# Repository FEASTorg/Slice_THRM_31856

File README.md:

<div align="center">
  <!-- Title: -->
  
  <h2><a href="https://github.com/uwo-fast/Slice_THRM"> Slice THRM </a></h2>
  <!-- Labels: -->
  <!-- First row: -->

  <a href="https://certification.oshwa.org/">
    
    <!-- img src="https://img.shields.io/badge/OSHWA-Certified-darkgreen?style=flat-square" height="20" alt="OSHWA" -->       <!-- img src="https://img.shields.io/badge/OSHWA-Pending-darkorange?style=flat-square" height="20" alt="OSHWA" -->
  </a>

  <!-- Second row: -->
  <br>

  <!-- Short description: -->
  <h3>Thermocouple Reader Slice for BREAD.</h3>
</div>

## Introduction
A BREAD slice that reads four thermocouples. Each channel has its own
MAX31856 (cold-junction compensated, linearized, types B/E/J/K/N/R/S/T),
read by the slice's Arduino Nano over one shared SPI bus.

## Project Overview

### Channels

| Channel | Terminal | Converter | Nano CS | Nano DRDY | FAULT (through U2) |
| ------- | -------- | --------- | ------- | --------- | ------------------ |
| 1 | J4 (pin 1 T+, pin 2 T-) | U4 | D6 | A3 | A7 with D10 low |
| 2 | J5 | U5 | D7 | A2 | A7 with D10 high |
| 3 | J6 | U6 | D8 | A1 | A6 with D10 low |
| 4 | J7 | U7 | D9 | A0 | A6 with D10 high |

FAULT and DRDY are active low. The four FAULT lines reach the Nano's
analog-only pins A6/A7 through U2 (CD74HC4053): D10 drives S1 and S2
together, so one D10 level selects channels 1 and 3, the other 2 and 4.
FAULT1-4 have 10k pull-ups to 3.3 V, so an idle line reads about 3.3 V
on the 0-5 V ADC and an asserted fault reads near 0 V.

### SPI

- Shared SCK (D13), SDI/MOSI (D11), SDO/MISO (D12); one CS per channel.
- SPI mode 1 or 3: the MAX31856 needs CPHA = 1 and accepts either
  clock polarity (data sheet 19-7534 Rev 0, Table 5).
- SCK up to 4 MHz (16 MHz / 4). The MAX31856 allows 5 MHz; the level
  buffers add a few ns each way, so check SDO timing on the bench before
  going faster than 4 MHz.
- D10 is the AVR's hardware SS pin; it is an output here (FAULT_SW), which
  keeps the SPI peripheral in master mode.

### 3.3 V domain and level shifting

The MAX31856s run from +3V3 (U3, MIC5225-3.3, 150 mA). The Nano is 5 V.

- U8 (74LVC245A, on +3V3) passes CS1-4, SCK and SDI from the Nano to the
  converters at 3.3 V. Its inputs accept 5 V.
- U9 (74AHCT245, on +5V) passes SDO and DRDY1-4 back to the Nano. Its TTL
  inputs (VIH 2.0 V) read the 3.3 V outputs with margin.
- R21-R24 hold CS1-4 high while the Nano is in reset, so no converter is
  selected. R25 (10k) holds SDO low when no converter drives it.
- U9 drives the Nano's MISO (D12) at all times: program the Nano over USB,
  not through an ICSP header plugged into the Nano.

### Qwiic (J1)

J1 is a 3.3 V Qwiic port. Its supply pin is on +3V3 (U3), and U10
(PCA9306) translates between it and the slice's 5 V I2C bus (A4/A5 and
the bus connector). R33/R34 pull the 5 V side up to +5V and R31/R32 pull
the Qwiic side up to +3V3. U10's EN and VREF2 are tied and held at +5V
through R30 (200k), with C31 (100 pF) on VREF2, so the translator is
always on.

The Qwiic device's current comes from U3 (150 mA), which also feeds the
four MAX31856s and U8.

### Firmware

`firmware/` is empty; firmware is tracked separately.

## Installation
[Provide instructions for installing any necessary software or hardware components.]

## Usage
[Explain how to use the project. Include examples and screenshots if applicable.]

### Basic Usage
[Provide basic usage instructions.]

### Advanced Usage
[Provide advanced usage instructions, including any optional features or configurations.]

## Documentation
[Link to the detailed documentation if available. Provide instructions on how to access and navigate the documentation.]

## Contributing
[Explain how others can contribute to the project. Include guidelines for submitting issues, pull requests, and any coding standards.]

### Code of Conduct
[Link to the project's code of conduct if available.]

## License
[State the license under which the project is distributed. Include a link to the full license text.]

## Acknowledgements
[Acknowledge any contributors, collaborators, funding sources, or organizations that supported the project.]

## Contact
[Provide contact information for the project maintainer(s) or lead researcher(s). Include an email address or a link to a contact form.]

---

<div align="center">
  
</div>

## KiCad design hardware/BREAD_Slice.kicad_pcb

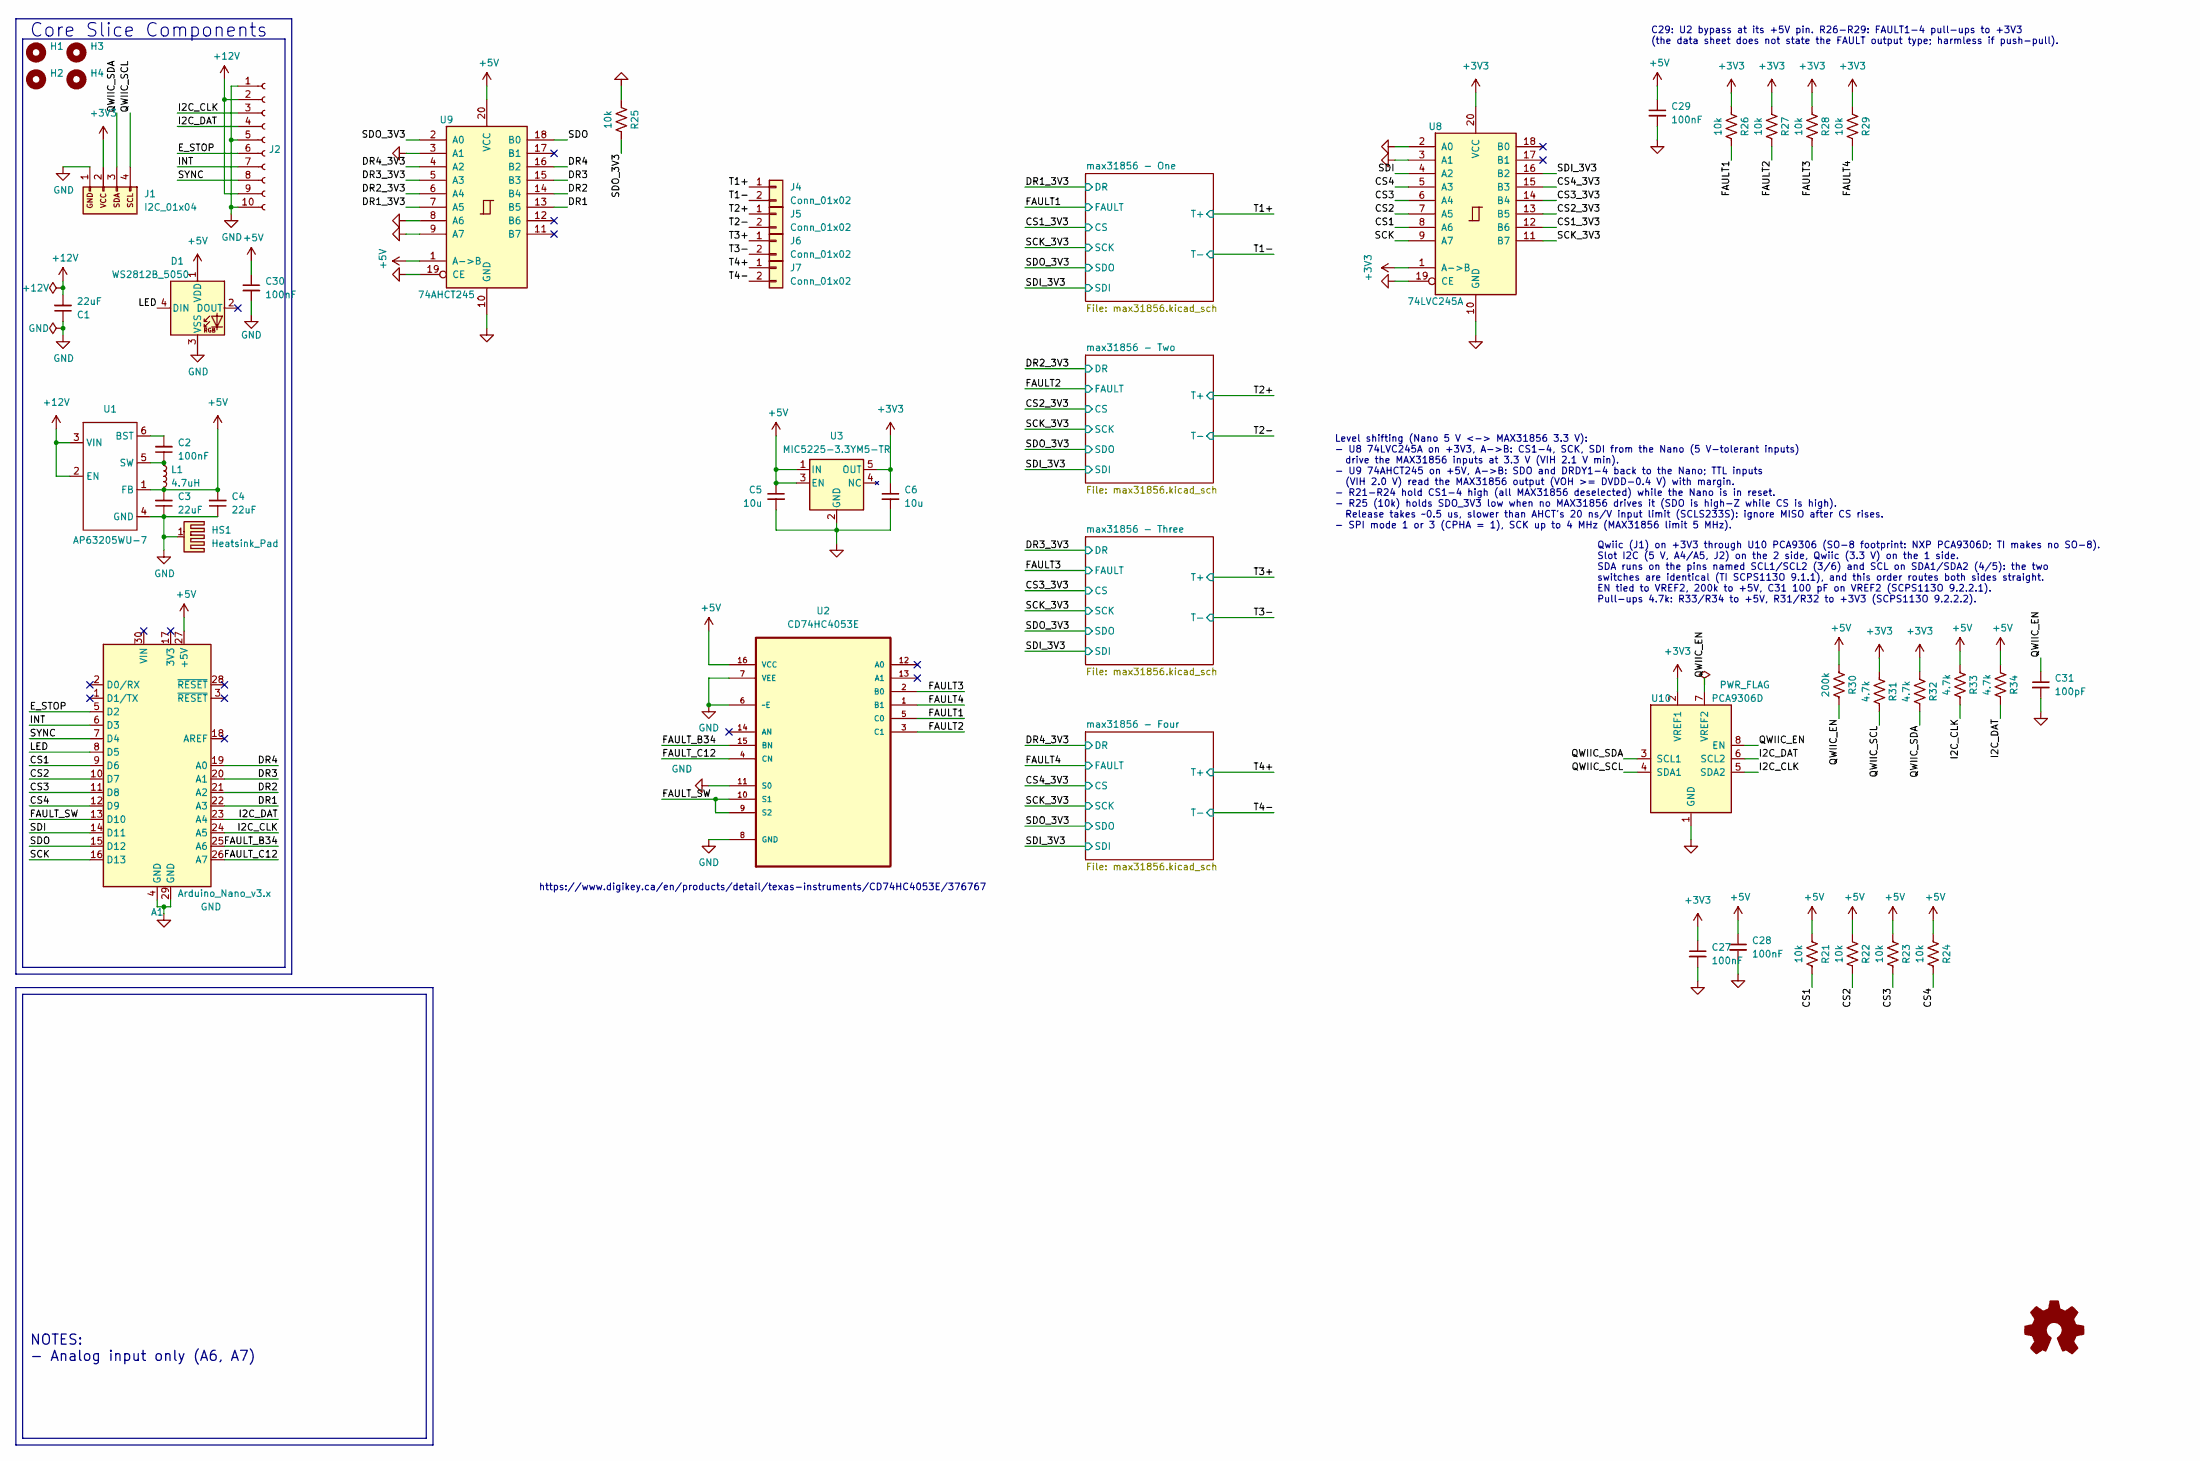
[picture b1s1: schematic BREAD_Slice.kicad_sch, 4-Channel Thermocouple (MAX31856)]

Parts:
A1: Arduino_Nano_v3.x; Arduino_Nano
C1, C3, C4: 22uF; C_1206_3216Metric
C2: 100nF; C_1206_3216Metric
C5, C6: 10u; C_1206_3216Metric
C27, C28, C29, C30: 100nF; C_0805_2012Metric
C31: 100pF; C_0603_1608Metric
D1: WS2812B_5050; WS2812-5050-4PIN
H1, H2, H3, H4: MountingHole; MountingHole_5mm
HS1: Heatsink_Pad; Thermal_Pad
J1: I2C_01x04; JST_SH_SM04B-SRSS-TB_1x04-1MP_P1.00mm_Horizontal
J2: Conn_01x10_Female; PinSocket_1x10_P2.54mm_Horizontal
J4, J5, J6, J7: Conn_01x02; TerminalBlock_4Ucon_1x02_P3.50mm_Horizontal
L1: 4.7uH; L_1210_3225Metric
R21, R22, R23, R24, R25, R26, R27, R28, R29: 10k; R_0805_2012Metric
R30: 200k; R_0805_2012Metric
R31, R32, R33, R34: 4.7k; R_0805_2012Metric
U1: AP63205WU-7; TSOT-23-6
U2: CD74HC4053E; DIP254P762X508-16; MPN CD74HC4053E
U3: MIC5225-3.3YM5-TR; SOT-23-5
U8: 74LVC245A; TSSOP-20_4.4x6.5mm_P0.65mm
U9: 74AHCT245; TSSOP-20_4.4x6.5mm_P0.65mm
U10: PCA9306D; SO-8_3.9x4.9mm_P1.27mm

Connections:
+3V3: C6.1, C27.1, J1.2, R26.1, R27.1, R28.1, R29.1, R31.1, R32.1, U3.5 (OUT), U8.1 (A->B), U8.20 (VCC), U10.2 (VREF1); also elsewhere on the board
+5V: A1.27 (+5V), C3.2, C4.2, C5.1, C28.1, C29.1, C30.1, D1.1 (VDD), L1.2, R21.1, R22.1, R23.1, R24.1, R30.1, R33.1, R34.1, U1.1 (FB), U2.16 (VCC), U3.1 (IN), U3.3 (EN), U9.1 (A->B), U9.20 (VCC)
+12V: C1.2, J2.2, J2.9, U1.2 (EN), U1.3 (VIN)
/CS1: A1.9 (D6), R21.2, U8.8 (A6)
/CS1_3V3: U8.12 (B6); also elsewhere on the board
/CS2: A1.10 (D7), R22.2, U8.7 (A5)
/CS2_3V3: U8.13 (B5); also elsewhere on the board
/CS3: A1.11 (D8), R23.2, U8.6 (A4)
/CS3_3V3: U8.14 (B4); also elsewhere on the board
/CS4: A1.12 (D9), R24.2, U8.5 (A3)
/CS4_3V3: U8.15 (B3); also elsewhere on the board
/DR1: A1.22 (A3), U9.13 (B5)
/DR1_3V3: U9.7 (A5); also elsewhere on the board
/DR2: A1.21 (A2), U9.14 (B4)
/DR2_3V3: U9.6 (A4); also elsewhere on the board
/DR3: A1.20 (A1), U9.15 (B3)
/DR3_3V3: U9.5 (A3); also elsewhere on the board
/DR4: A1.19 (A0), U9.16 (B2)
/DR4_3V3: U9.4 (A2); also elsewhere on the board
/E_STOP: A1.5 (D2), J2.6
/FAULT1: R26.2, U2.5 (C0); also elsewhere on the board
/FAULT2: R27.2, U2.3 (C1); also elsewhere on the board
/FAULT3: R28.2, U2.2 (B0); also elsewhere on the board
/FAULT4: R29.2, U2.1 (B1); also elsewhere on the board
/FAULT_B34: A1.25 (A6), U2.15 (BN)
/FAULT_C12: A1.26 (A7), U2.4 (CN)
/FAULT_SW: A1.13 (D10), U2.9 (S2), U2.10 (S1)
/I2C_CLK: A1.24 (A5), J2.3, R33.2, U10.5 (SDA2)
/I2C_DAT: A1.23 (A4), J2.4, R34.2, U10.6 (SCL2)
/INT: A1.6 (D3), J2.7
/LED: A1.8 (D5), D1.4 (DIN)
/QWIIC_EN: C31.1, R30.2, U10.7 (VREF2), U10.8 (EN)
/QWIIC_SCL: J1.4, R31.2, U10.4 (SDA1)
/QWIIC_SDA: J1.3, R32.2, U10.3 (SCL1)
/SCK: A1.16 (D13), U8.9 (A7)
/SCK_3V3: U8.11 (B7); also elsewhere on the board
/SDI: A1.14 (D11), U8.4 (A2)
/SDI_3V3: U8.16 (B2); also elsewhere on the board
/SDO: A1.15 (D12), U9.18 (B0)
/SDO_3V3: R25.2, U9.2 (A0); also elsewhere on the board
/SYNC: A1.7 (D4), J2.8
/T1+: J4.1; also elsewhere on the board
/T1-: J4.2; also elsewhere on the board
/T2+: J5.1; also elsewhere on the board
/T2-: J5.2; also elsewhere on the board
/T3+: J6.1; also elsewhere on the board
/T3-: J6.2; also elsewhere on the board
/T4+: J7.1; also elsewhere on the board
/T4-: J7.2; also elsewhere on the board
GND: A1.4 (GND), A1.29 (GND), C1.1, C3.1, C4.1, C5.2, C6.2, C27.2, C28.2, C29.2, C30.2, C31.2, D1.3 (VSS), HS1.1, J1.1, J2.1, J2.5, J2.10, R25.1, U1.4 (GND), U2.6 (~E), U2.7 (VEE), U2.8 (GND), U2.11 (S0), U3.2 (GND), U8.2 (A0), U8.3 (A1), U8.10 (GND), U8.19 (CE), U9.3 (A1), U9.8 (A6), U9.9 (A7), U9.10 (GND), U9.19 (CE), U10.1 (GND); also elsewhere on the board
unnamed: C2.2, U1.6 (BST)
unnamed: C2.1, L1.1, U1.5 (SW)

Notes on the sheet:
NOTES: - Analog input only (A6, A7)
Core Slice Components
https://www.digikey.ca/en/products/detail/texas-instruments/CD74HC4053E/376767
Level shifting (Nano 5 V <-> MAX31856 3.3 V): - U8 74LVC245A on +3V3, A->B: CS1-4, SCK, SDI from the Nano (5 V-tolerant inputs) drive the MAX31856 inputs at 3.3 V (VIH 2.1 V min). - U9 74AHCT245 on +5V, A->B: SDO and DRDY1-4 back to the Nano; TTL inputs (VIH 2.0 V) read the MAX31856 output (VOH >= 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
C29: U2 bypass at its +5V pin. R26-R29: FAULT1-4 pull-ups to +3V3 (the data sheet does not state the FAULT output type; harmless if push-pull).
Qwiic (J1) on +3V3 through U10 PCA9306 (SO-8 footprint: NXP PCA9306D; TI makes no SO-8). Slot I2C (5 V, A4/A5, J2) on the 2 side, Qwiic (3.3 V) on the 1 side. SDA runs on the pins named SCL1/SCL2 (3/6) and SCL on SDA1/SDA2 (4/5): the two switches are identical (TI SCPS113O 9.1.1), and this order ro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

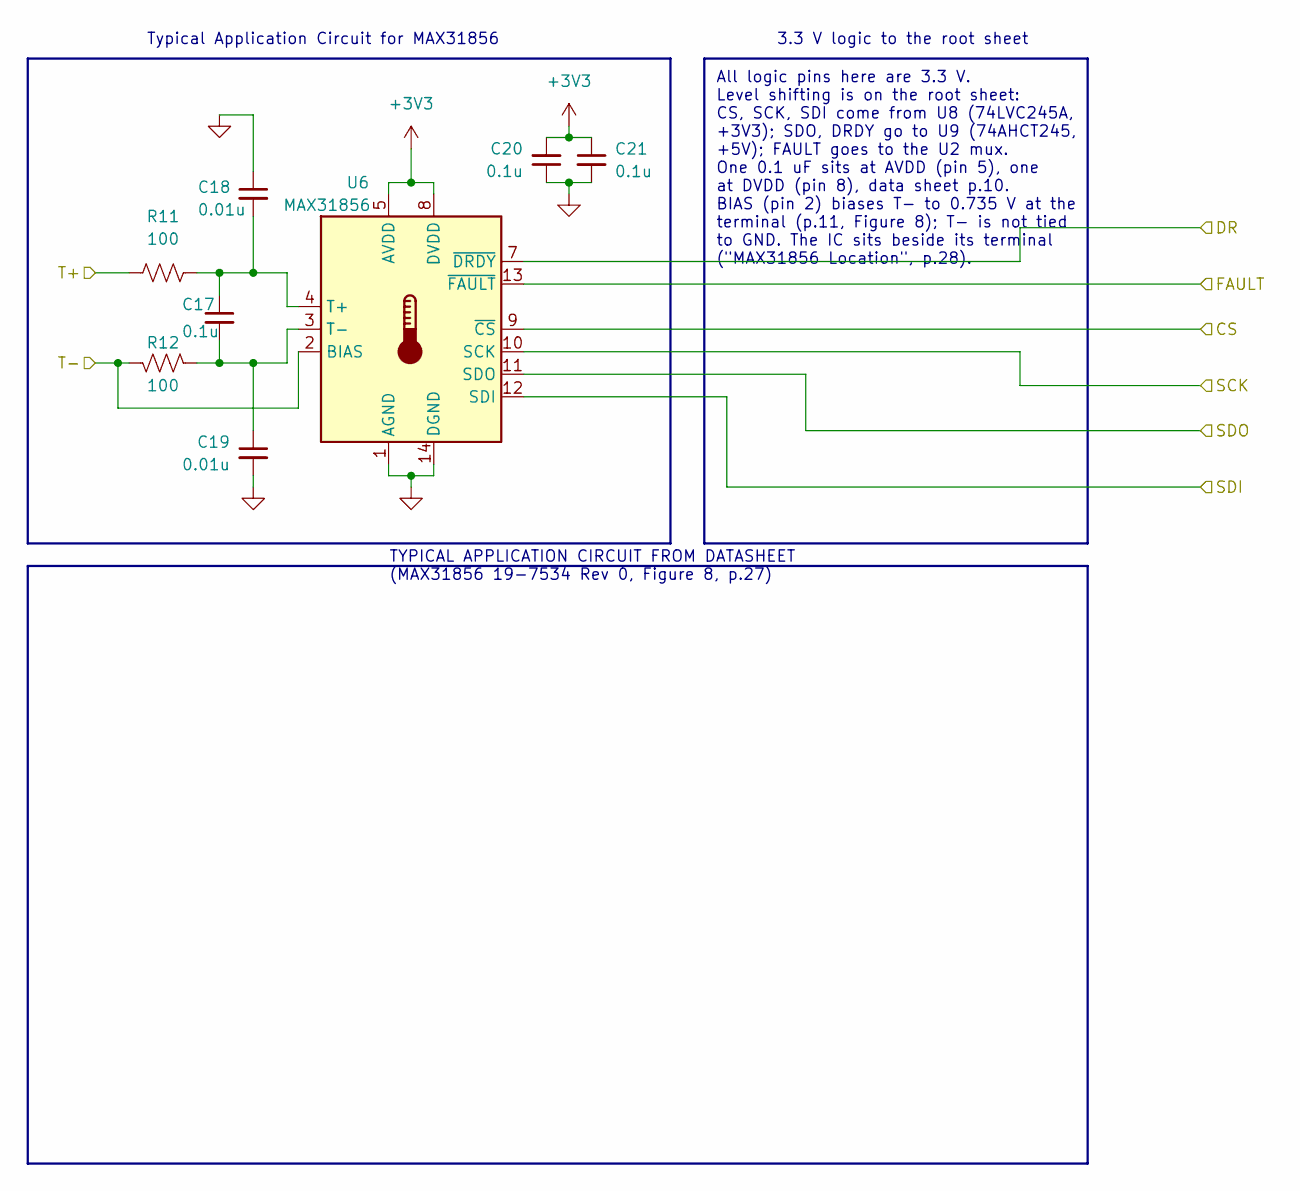
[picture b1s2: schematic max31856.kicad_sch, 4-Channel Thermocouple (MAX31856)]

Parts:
C17, C20, C21: 0.1u; C_1206_3216Metric
C18, C19: 0.01u; C_1206_3216Metric
R11, R12: 100; R_1206_3216Metric
U6: MAX31856; TSSOP-14_4.4x5mm_P0.65mm

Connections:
+3V3: C20.2, C21.1, U6.5 (AVDD), U6.8 (DVDD); also elsewhere on the board
/CS3_3V3: U6.9 (~CS); also elsewhere on the board
/DR3_3V3: U6.7 (~DRDY); also elsewhere on the board
/FAULT3: U6.13 (~FAULT); also elsewhere on the board
/SCK_3V3: U6.10 (SCK); also elsewhere on the board
/SDI_3V3: U6.12 (SDI); also elsewhere on the board
/SDO_3V3: U6.11 (SDO); also elsewhere on the board
/T3+: R11.1; also elsewhere on the board
/T3-: R12.1, U6.2 (BIAS); also elsewhere on the board
GND: C18.1, C19.2, C20.1, C21.2, U6.1 (AGND), U6.14 (DGND); also elsewhere on the board
unnamed: C17.1, C18.2, R11.2, U6.4 (T+)
unnamed: C17.2, C19.1, R12.2, U6.3 (T-)

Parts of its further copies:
C7, C10, C11, C12, C15, C16, C22, C25, C26: 0.1u; C_1206_3216Metric
C8, C9, C13, C14, C23, C24: 0.01u; C_1206_3216Metric
R1, R2, R6, R7, R16, R17: 100; R_1206_3216Metric
U4, U5, U7: MAX31856; TSSOP-14_4.4x5mm_P0.65mm

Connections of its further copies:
+3V3: C10.2, C11.1, C15.2, C16.1, C25.2, C26.1, U4.5 (AVDD), U4.8 (DVDD), U5.5 (AVDD), U5.8 (DVDD), U7.5 (AVDD), U7.8 (DVDD); also elsewhere on the board
/CS1_3V3: U4.9 (~CS); also elsewhere on the board
/CS2_3V3: U5.9 (~CS); also elsewhere on the board
/CS4_3V3: U7.9 (~CS); also elsewhere on the board
/DR1_3V3: U4.7 (~DRDY); also elsewhere on the board
/DR2_3V3: U5.7 (~DRDY); also elsewhere on the board
/DR4_3V3: U7.7 (~DRDY); also elsewhere on the board
/FAULT1: U4.13 (~FAULT); also elsewhere on the board
/FAULT2: U5.13 (~FAULT); also elsewhere on the board
/FAULT4: U7.13 (~FAULT); also elsewhere on the board
/SCK_3V3: U4.10 (SCK), U5.10 (SCK), U7.10 (SCK); also elsewhere on the board
/SDI_3V3: U4.12 (SDI), U5.12 (SDI), U7.12 (SDI); also elsewhere on the board
/SDO_3V3: U4.11 (SDO), U5.11 (SDO), U7.11 (SDO); also elsewhere on the board
/T1+: R1.1; also elsewhere on the board
/T1-: R2.1, U4.2 (BIAS); also elsewhere on the board
/T2+: R6.1; also elsewhere on the board
/T2-: R7.1, U5.2 (BIAS); also elsewhere on the board
/T4+: R16.1; also elsewhere on the board
/T4-: R17.1, U7.2 (BIAS); also elsewhere on the board
GND: C8.1, C9.2, C10.1, C11.2, C13.1, C14.2, C15.1, C16.2, C23.1, C24.2, C25.1, C26.2, U4.1 (AGND), U4.14 (DGND), U5.1 (AGND), U5.14 (DGND), U7.1 (AGND), U7.14 (DGND); also elsewhere on the board
unnamed: C7.1, C8.2, R1.2, U4.4 (T+)
unnamed: C7.2, C9.1, R2.2, U4.3 (T-)
unnamed: C12.1, C13.2, R6.2, U5.4 (T+)
unnamed: C12.2, C14.1, R7.2, U5.3 (T-)
unnamed: C22.1, C23.2, R16.2, U7.4 (T+)
unnamed: C22.2, C24.1, R17.2, U7.3 (T-)

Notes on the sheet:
3.3 V logic to the root sheet
Typical Application Circuit for MAX31856
TYPICAL APPLICATION CIRCUIT FROM DATASHEET (MAX31856 19-7534 Rev 0, Figure 8, p.27)
All logic pins here are 3.3 V. Level shifting is on the root sheet: CS, SCK, SDI come from U8 (74LVC245A, +3V3); SDO, DRDY go to U9 (74AHCT245, +5V); FAULT goes to the U2 mux. One 0.1 uF sits at AVDD (pin 5), one at DVDD (pin 8), data sheet p.10. BIAS (pin 2) biases T- to 0.735 V at the terminal (p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

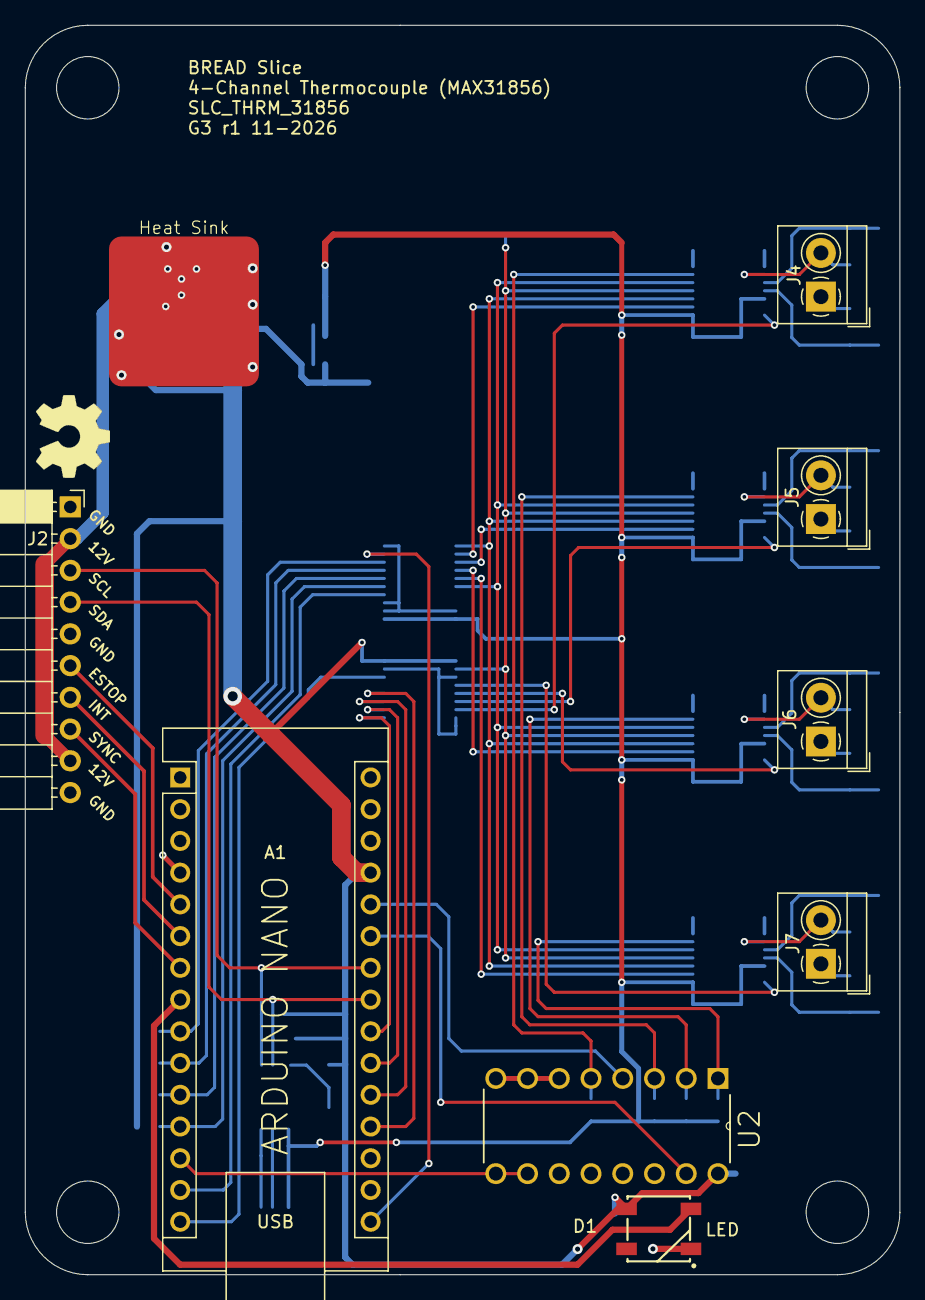
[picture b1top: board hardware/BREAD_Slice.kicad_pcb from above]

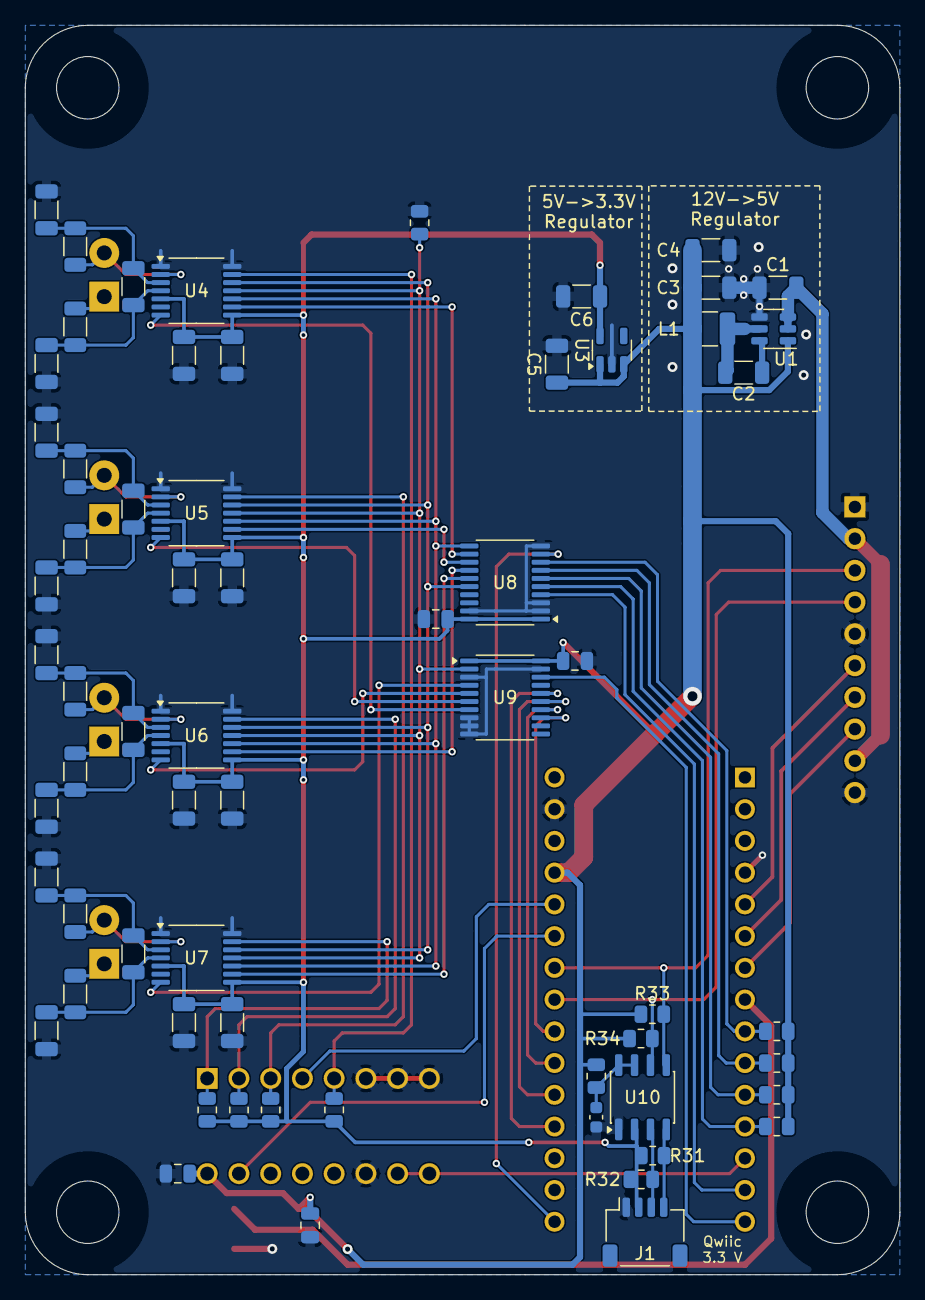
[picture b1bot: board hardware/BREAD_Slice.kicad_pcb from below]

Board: 2 copper layers, 70.0 x 100.0 mm, 78 parts (64 on the bottom side), 60 nets.

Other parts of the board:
Logo1: Logo_Open_Hardware_Small; OSHW-Symbol_6.7x6mm_SilkScreen

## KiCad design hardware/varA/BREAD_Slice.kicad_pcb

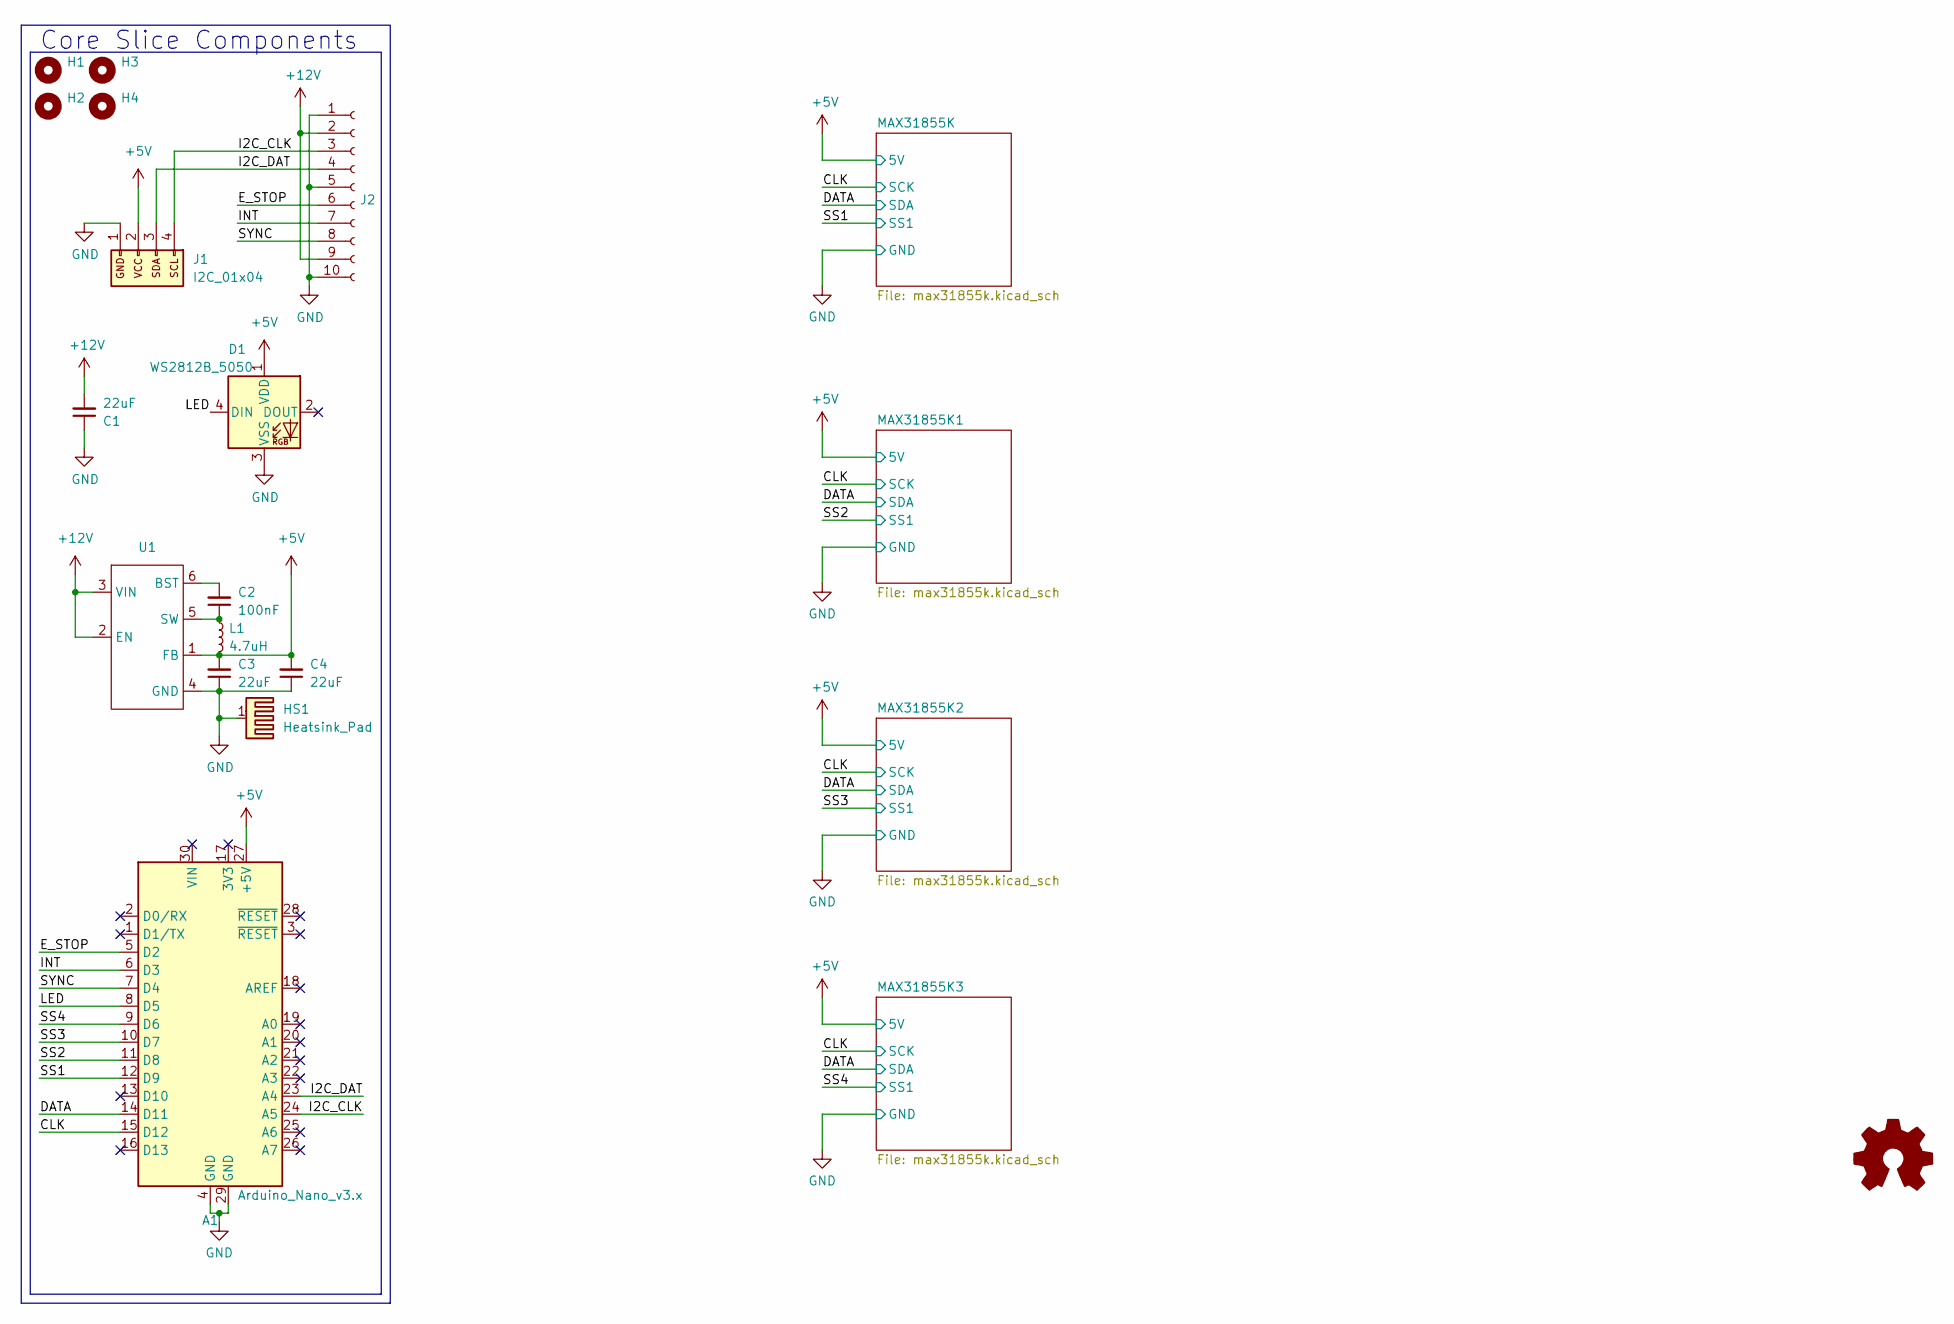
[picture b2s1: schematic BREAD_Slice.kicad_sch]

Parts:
A1: Arduino_Nano_v3.x; Arduino_Nano
C1, C3, C4: 22uF; C_1206_3216Metric
C2: 100nF; C_1206_3216Metric
D1: WS2812B_5050; WS2812-5050-4PIN
H1, H2, H3, H4: MountingHole; MountingHole_5mm
HS1: Heatsink_Pad; Thermal Pad
J1: I2C_01x04; JST_SH_SM04B-SRSS-TB_1x04-1MP_P1.00mm_Horizontal
J2: Conn_01x10_Female; PinSocket_1x10_P2.54mm_Horizontal
L1: 4.7uH; L_1210_3225Metric
U1: TSOT-23-6

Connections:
+5V: A1.27 (+5V), C3.2, C4.2, D1.1 (VDD), J1.2, L1.2, U1.1 (FB); also elsewhere on the board
+12V: C1.2, J2.2, J2.9, U1.2 (EN), U1.3 (VIN)
/CLK: A1.15 (D12); also elsewhere on the board
/DATA: A1.14 (D11); also elsewhere on the board
/E_STOP: A1.5 (D2), J2.6
/I2C_CLK: A1.24 (A5), J1.4, J2.3
/I2C_DAT: A1.23 (A4), J1.3, J2.4
/INT: A1.6 (D3), J2.7
/LED: A1.8 (D5), D1.4 (DIN)
/SS1: A1.12 (D9); also elsewhere on the board
/SS2: A1.11 (D8); also elsewhere on the board
/SS3: A1.10 (D7); also elsewhere on the board
/SS4: A1.9 (D6); also elsewhere on the board
/SYNC: A1.7 (D4), J2.8
GND: A1.4 (GND), A1.29 (GND), C1.1, C3.1, C4.1, D1.3 (VSS), HS1.1, J1.1, J2.1, J2.5, J2.10, U1.4 (GND); also elsewhere on the board
unnamed: C2.2, U1.6 (BST)
unnamed: C2.1, L1.1, U1.5 (SW)

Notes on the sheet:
Core Slice Components

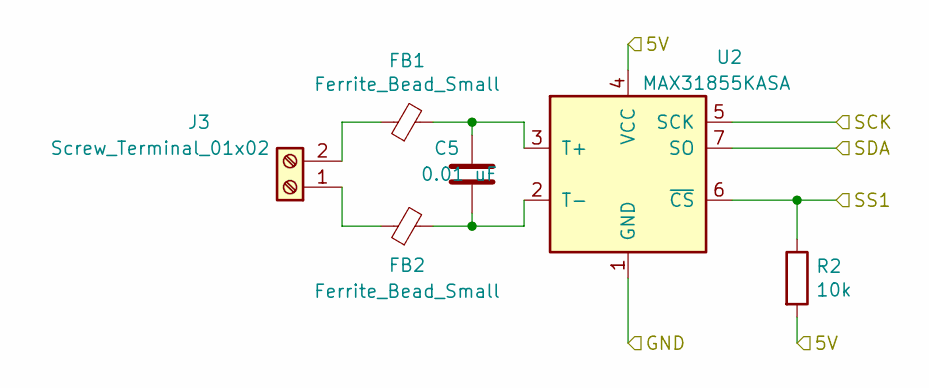
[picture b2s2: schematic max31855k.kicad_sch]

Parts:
C5: 0.01 uF; C_1206_3216Metric_Pad1.33x1.80mm_HandSolder
FB1, FB2: Ferrite_Bead_Small; R_1206_3216Metric_Pad1.30x1.75mm_HandSolder
J3: Screw_Terminal_01x02; TerminalBlock_TE_282834-2_1x02_P2.54mm_Horizontal
R2: 10k; R_1206_3216Metric_Pad1.30x1.75mm_HandSolder
U2: MAX31855KASA; SOIC-8_3.9x4.9mm_P1.27mm

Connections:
+5V: R2.2, U2.4 (VCC); also elsewhere on the board
/CLK: U2.5 (SCK); also elsewhere on the board
/DATA: U2.7 (SO); also elsewhere on the board
/SS1: R2.1, U2.6 (~CS); also elsewhere on the board
GND: U2.1 (GND); also elsewhere on the board
unnamed: FB2.1, J3.1
unnamed: FB1.1, J3.2
unnamed: C5.1, FB1.2, U2.3 (T+)
unnamed: C5.2, FB2.2, U2.2 (T-)

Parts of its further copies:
C6, C7, C8: 0.01 uF; C_1206_3216Metric_Pad1.33x1.80mm_HandSolder
FB3, FB4, FB5, FB6, FB7, FB8: Ferrite_Bead_Small; R_1206_3216Metric_Pad1.30x1.75mm_HandSolder
J4, J5, J6: Screw_Terminal_01x02; TerminalBlock_TE_282834-2_1x02_P2.54mm_Horizontal
R3, R4, R5: 10k; R_1206_3216Metric_Pad1.30x1.75mm_HandSolder
U3, U4, U5: MAX31855KASA; SOIC-8_3.9x4.9mm_P1.27mm

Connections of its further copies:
+5V: R3.2, R4.2, R5.2, U3.4 (VCC), U4.4 (VCC), U5.4 (VCC); also elsewhere on the board
/CLK: U3.5 (SCK), U4.5 (SCK), U5.5 (SCK); also elsewhere on the board
/DATA: U3.7 (SO), U4.7 (SO), U5.7 (SO); also elsewhere on the board
/SS2: R3.1, U3.6 (~CS); also elsewhere on the board
/SS3: R4.1, U4.6 (~CS); also elsewhere on the board
/SS4: R5.1, U5.6 (~CS); also elsewhere on the board
GND: U3.1 (GND), U4.1 (GND), U5.1 (GND); also elsewhere on the board
unnamed: FB4.1, J4.1
unnamed: FB3.1, J4.2
unnamed: FB6.1, J5.1
unnamed: FB5.1, J5.2
unnamed: FB8.1, J6.1
unnamed: FB7.1, J6.2
unnamed: C6.1, FB3.2, U3.3 (T+)
unnamed: C6.2, FB4.2, U3.2 (T-)
unnamed: C7.1, FB5.2, U4.3 (T+)
unnamed: C7.2, FB6.2, U4.2 (T-)
unnamed: C8.1, FB7.2, U5.3 (T+)
unnamed: C8.2, FB8.2, U5.2 (T-)

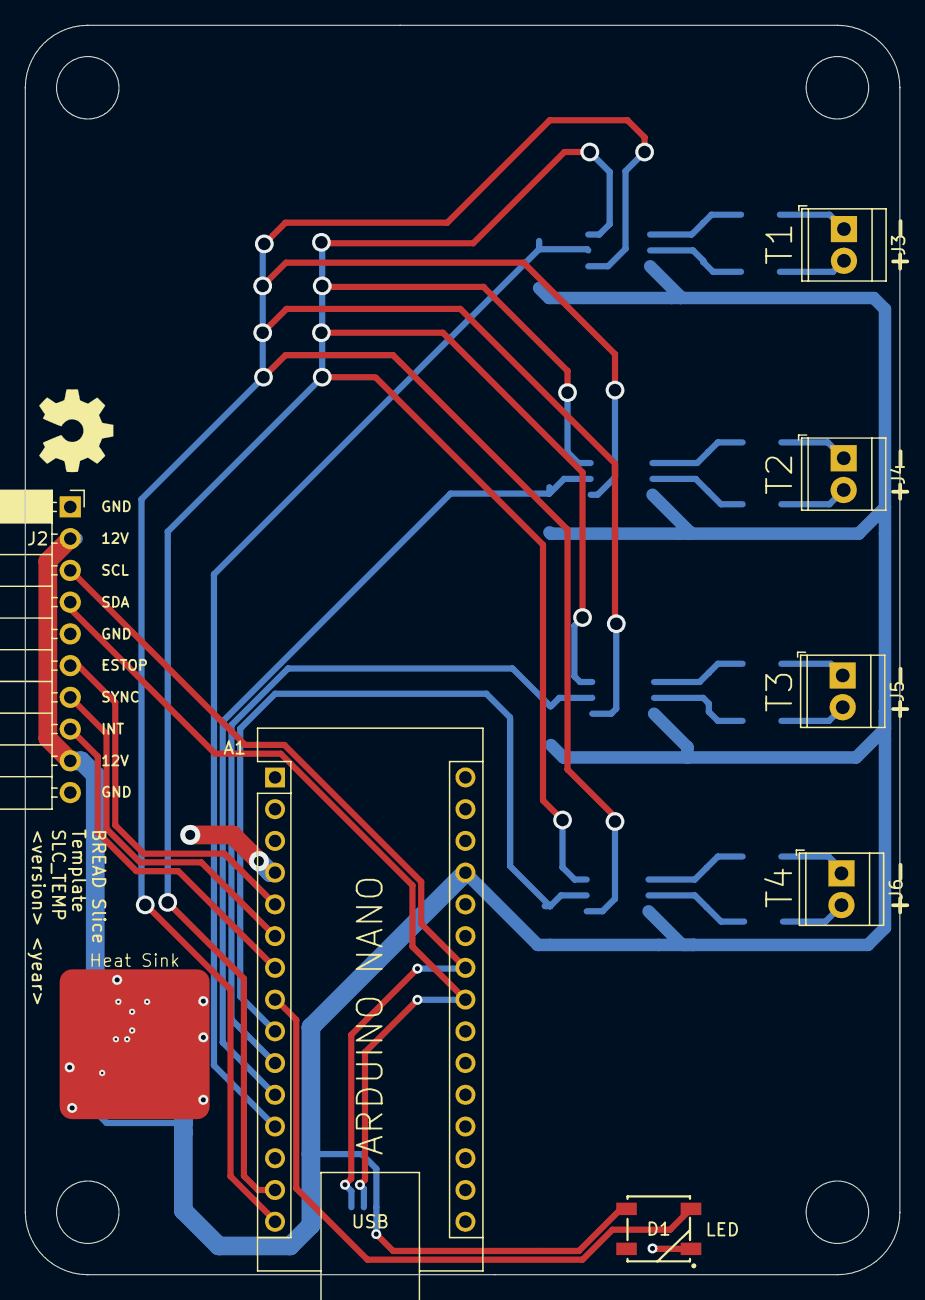
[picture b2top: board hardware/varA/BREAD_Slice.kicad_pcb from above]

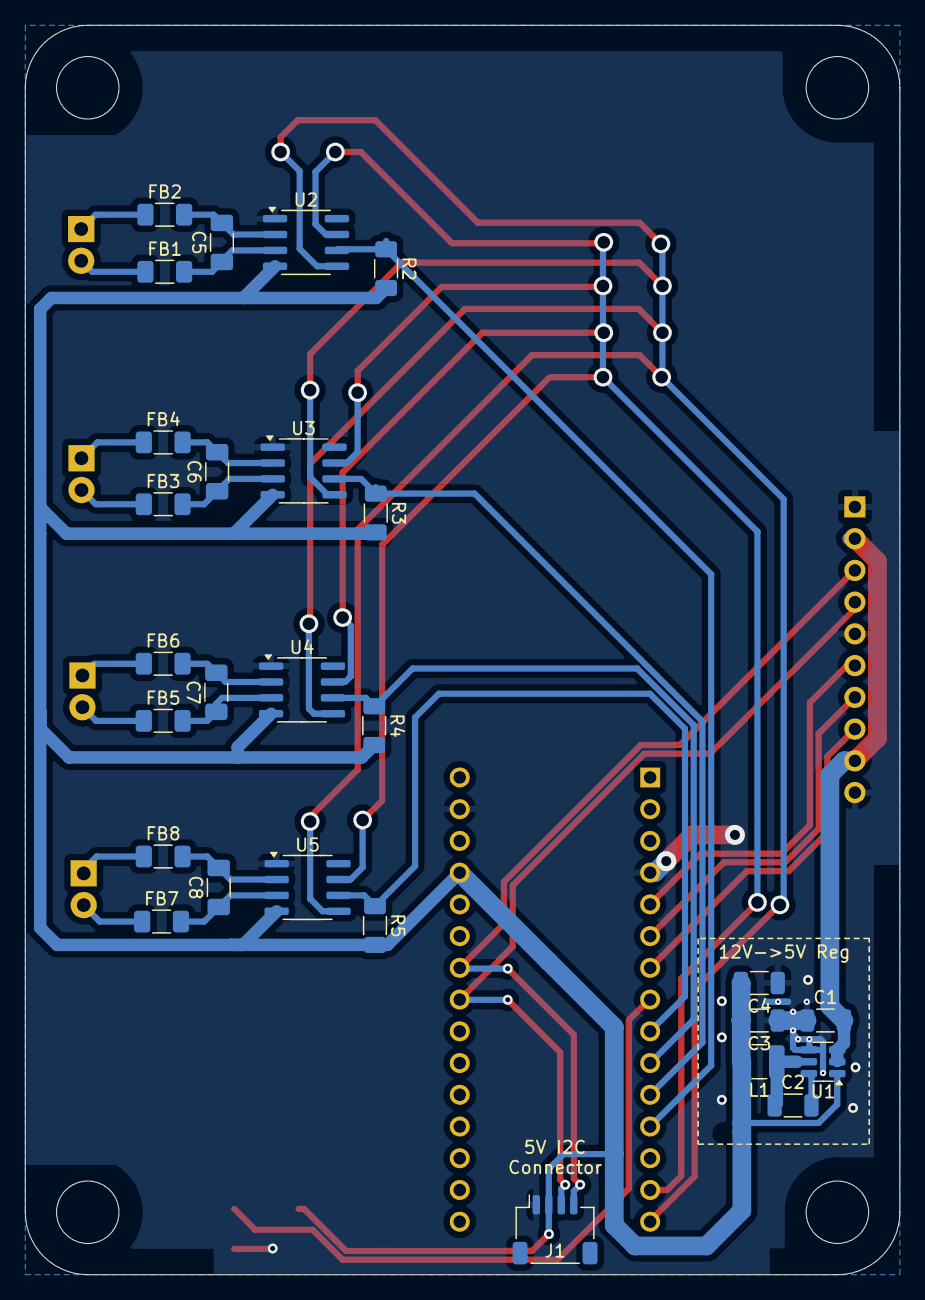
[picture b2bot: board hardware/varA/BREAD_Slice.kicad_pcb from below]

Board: 2 copper layers, 70.0 x 100.0 mm, 40 parts (27 on the bottom side), 33 nets.

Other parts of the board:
Logo1: Logo_Open_Hardware_Small; OSHW-Symbol_6.7x6mm_SilkScreen

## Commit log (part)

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2024-09-07 updated + checked schem and pcb with updated template
2024-09-12 removed unneeded top level 10k clk pull up (one on each max already
2025-04-19 minor tweaks
2025-09-25 clean out docs
2025-09-25 initial commit after split
2025-09-25 ci: add bread-infra pipeline and all docs template files
2025-09-25 hw: fix erc and drc errors; need to double check the diode and levelshift ic pathes can be independently toggled before prod
2025-09-25 📄 KiBot index + board renders (auto)
2026-04-20 refactor: org casing rename from 'FEASTorg' to 'feastorg'
2026-05-20 Add slice.yaml manifest (schema v1.0)
2026-05-24 Add TODO.md for consistency
2026-05-24 Standardize TODO.md with Pass 1/Pass 2 structure
